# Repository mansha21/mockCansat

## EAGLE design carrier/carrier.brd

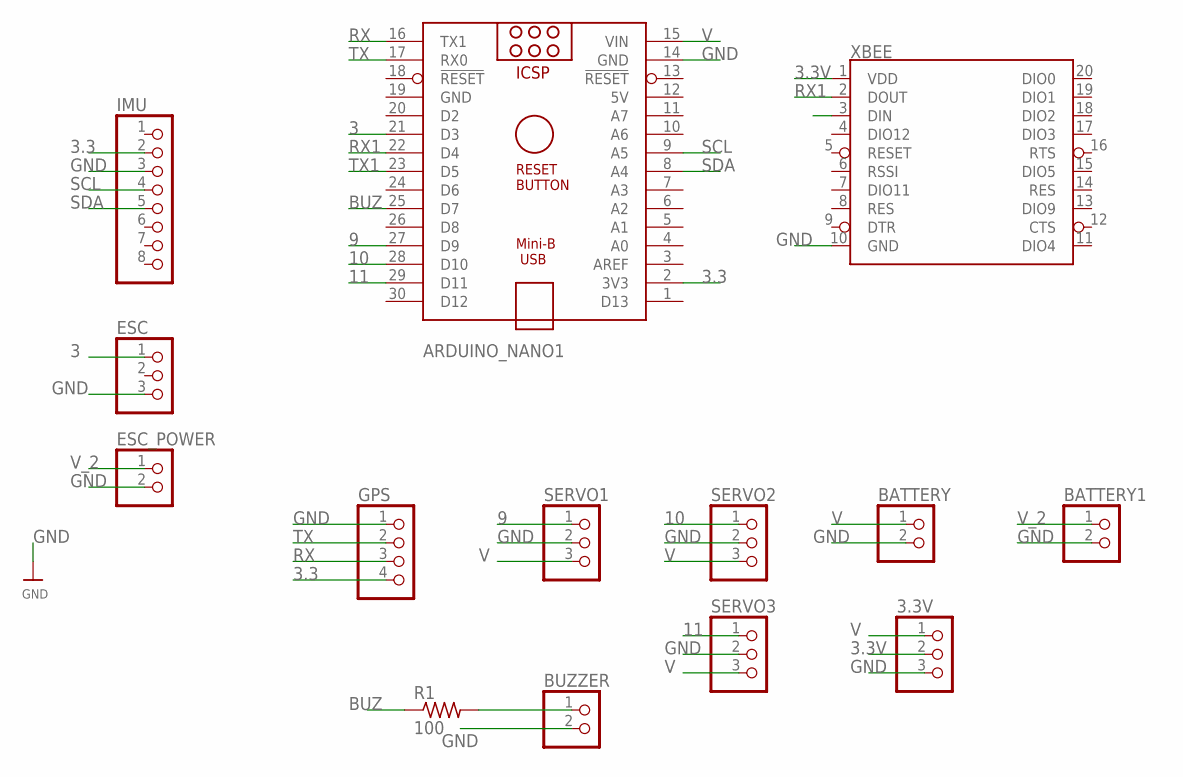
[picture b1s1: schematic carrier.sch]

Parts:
3.3V: PINHD-1X3; 1X03
ARDUINO_NANO1: ARDUINO_NANO
BATTERY, BATTERY1: PINHD-1X2; 1X02
BUZZER: PINHD-1X2; 1X02
ESC: PINHD-1X3; 1X03
ESC_POWER: PINHD-1X2; 1X02
GPS: PINHD-1X4; 1X04
IMU: PINHD-1X8; 1X08
R1: 100; M0805
SERVO1, SERVO2, SERVO3: PINHD-1X3; 1X03
XBEE: XBEE

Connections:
3: ARDUINO_NANO1.21 (D3), ESC.1
3.3: ARDUINO_NANO1.2 (3V3), GPS.4, IMU.2
3.3V: 3.3V.2, XBEE.1 (VDD)
5V: ARDUINO_NANO1.12 (5V)
9: ARDUINO_NANO1.27 (D9), SERVO1.1
10: ARDUINO_NANO1.28 (D10), SERVO2.1
11: ARDUINO_NANO1.29 (D11), SERVO3.1
BUZ: ARDUINO_NANO1.25 (D7), R1.1
GND: 3.3V.3, ARDUINO_NANO1.14 (GND), ARDUINO_NANO1.19 (GND), BATTERY.2, BATTERY1.2, BUZZER.2, ESC.3, ESC_POWER.2, GPS.1, IMU.3, SERVO1.2, SERVO2.2, SERVO3.2, XBEE.10 (GND)
unnamed: BUZZER.1, R1.2
RX: ARDUINO_NANO1.16 (TX1), GPS.3
RX1: ARDUINO_NANO1.22 (D4), XBEE.2 (DOUT)
SCL: ARDUINO_NANO1.9 (A5), IMU.4
SDA: ARDUINO_NANO1.8 (A4), IMU.5
TX: ARDUINO_NANO1.17 (RX0), GPS.2
TX1: ARDUINO_NANO1.23 (D5), XBEE.3 (DIN)
V: 3.3V.1, ARDUINO_NANO1.15 (VIN), BATTERY.1, SERVO1.3, SERVO2.3, SERVO3.3
V_2: BATTERY1.1, ESC_POWER.1

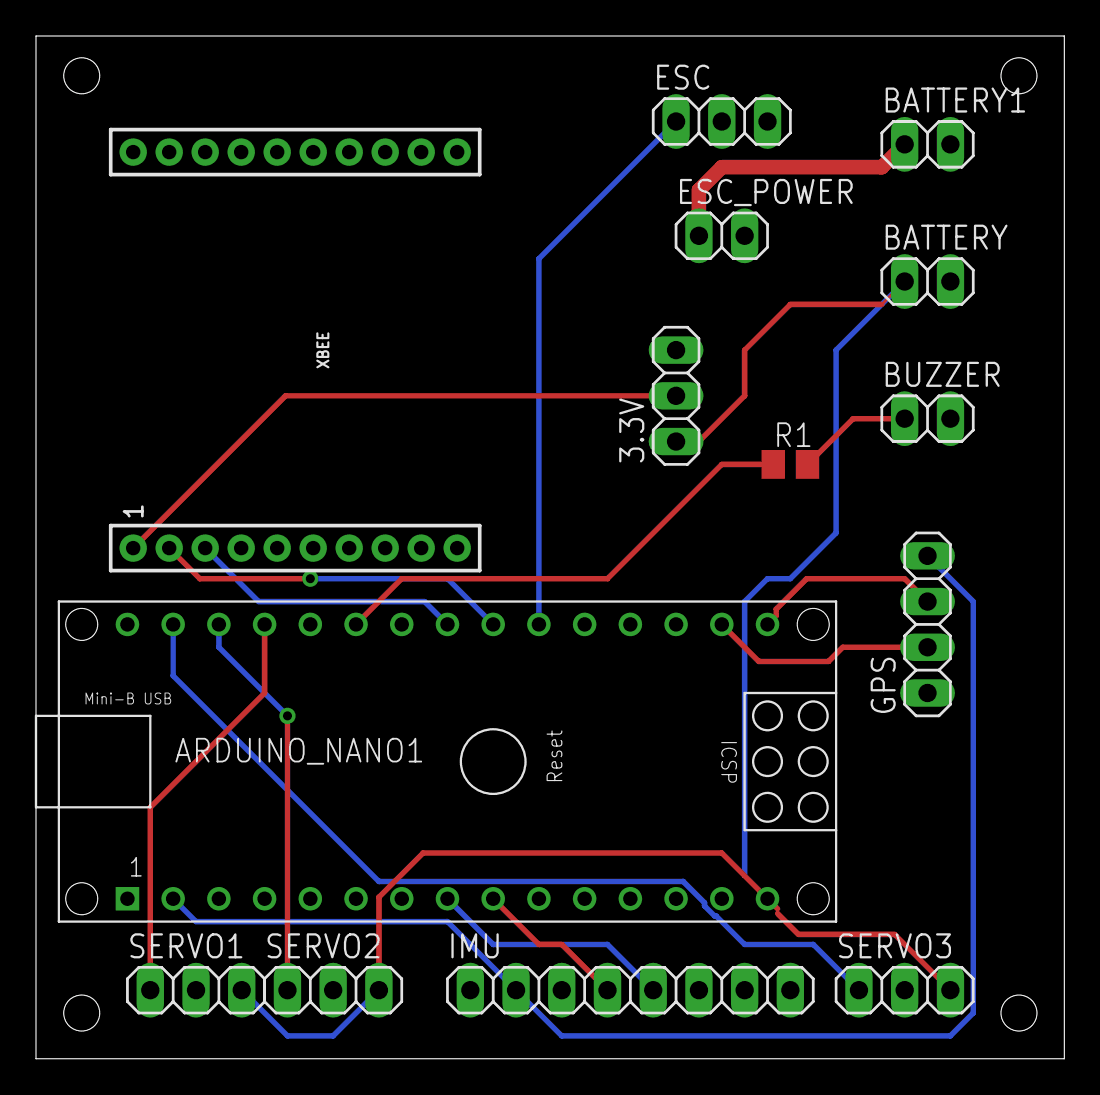
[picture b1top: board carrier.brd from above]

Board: 2 copper layers, 57.1 x 56.8 mm, 14 parts (0 on the bottom side), 17 nets.

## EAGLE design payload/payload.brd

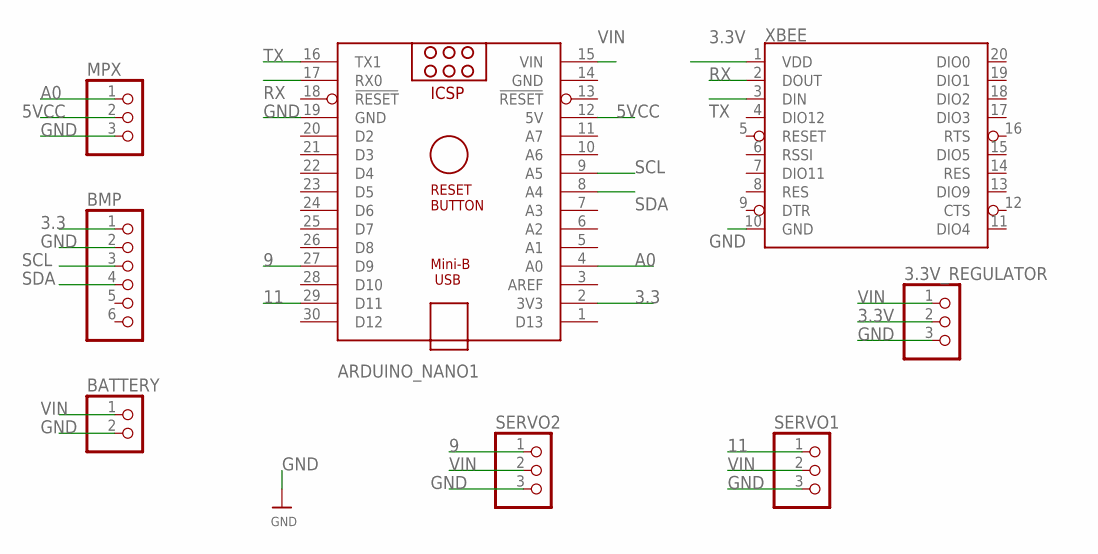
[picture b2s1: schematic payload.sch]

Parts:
3.3V_REGULATOR: PINHD-1X3; 1X03
ARDUINO_NANO1: ARDUINO_NANO
BATTERY: PINHD-1X2; 1X02
BMP: PINHD-1X6; 1X06
MPX: PINHD-1X3; 1X03
SERVO1, SERVO2: PINHD-1X3; 1X03
XBEE: XBEE

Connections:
3.3: ARDUINO_NANO1.2 (3V3), BMP.1
3.3V: 3.3V_REGULATOR.2, XBEE.1 (VDD)
5VCC: ARDUINO_NANO1.12 (5V), MPX.2
9: ARDUINO_NANO1.27 (D9), SERVO2.1
11: ARDUINO_NANO1.29 (D11), SERVO1.1
A0: ARDUINO_NANO1.4 (A0), MPX.1
GND: 3.3V_REGULATOR.3, ARDUINO_NANO1.14 (GND), ARDUINO_NANO1.19 (GND), BATTERY.2, BMP.2, MPX.3, SERVO1.3, SERVO2.3, XBEE.10 (GND)
RX: ARDUINO_NANO1.17 (RX0), XBEE.2 (DOUT)
SCL: ARDUINO_NANO1.9 (A5), BMP.3
SDA: ARDUINO_NANO1.8 (A4), BMP.4
TX: ARDUINO_NANO1.16 (TX1), XBEE.3 (DIN)
VIN: 3.3V_REGULATOR.1, ARDUINO_NANO1.15 (VIN), BATTERY.1, SERVO1.2, SERVO2.2

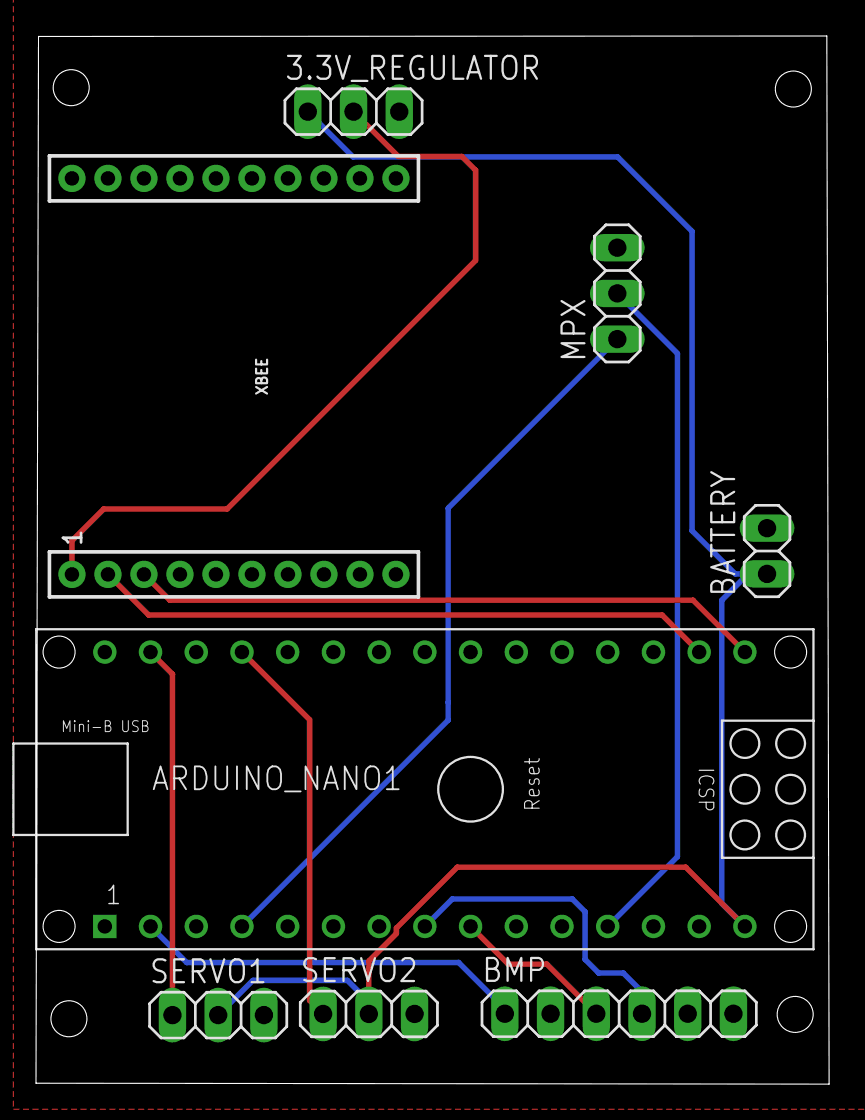
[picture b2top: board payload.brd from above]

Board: 2 copper layers, 44.1 x 58.2 mm, 8 parts (0 on the bottom side), 12 nets.

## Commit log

2021-05-20 test
2021-05-21 electrical repo updated
2021-05-21 electrical final
2021-05-21 deleting folder

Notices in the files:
parts and their libraries:
SparkFun-RF: Licensing: Creative Commons ShareAlike 4.0 International - https://creativecommons.org/licenses/by-sa/4.0
